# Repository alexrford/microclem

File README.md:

# microclem

`microclem` is a homebrew computer based around the WDC 65C02 processor. Physically, it uses the Eurocard (100x160mm) PCB form factor and type DIN 41612 type C connectors (64 or optionally 96 pin).

Currently only a barebones base board is designed. This board has only very basic functionality (memory, boot ROM, 65C22 for I/O over the external bus). It's designed to be expanded using other cards on a DIN 41612 backplane.

This is in an early stage of development and may not be functional yet.

## Credits

- DIN 41612 footprints are taken from the [official `kicad-footprints` repo](https://github.com/KiCad/kicad-footprints)
- System/bus clock switching component taken from an [EE times article by Rafey Mahmud](https://www.eetimes.com/techniques-to-make-clock-switching-glitch-free/)
- [Ben Eater's 6502 computer](https://eater.net/6502) was the initial inspiration for this project
- Arduino monitor PCB layout based on measurements from [Wayne and Layne](https://www.wayneandlayne.com/blog/2010/12/19/nice-drawings-of-the-arduino-uno-and-mega-2560/)

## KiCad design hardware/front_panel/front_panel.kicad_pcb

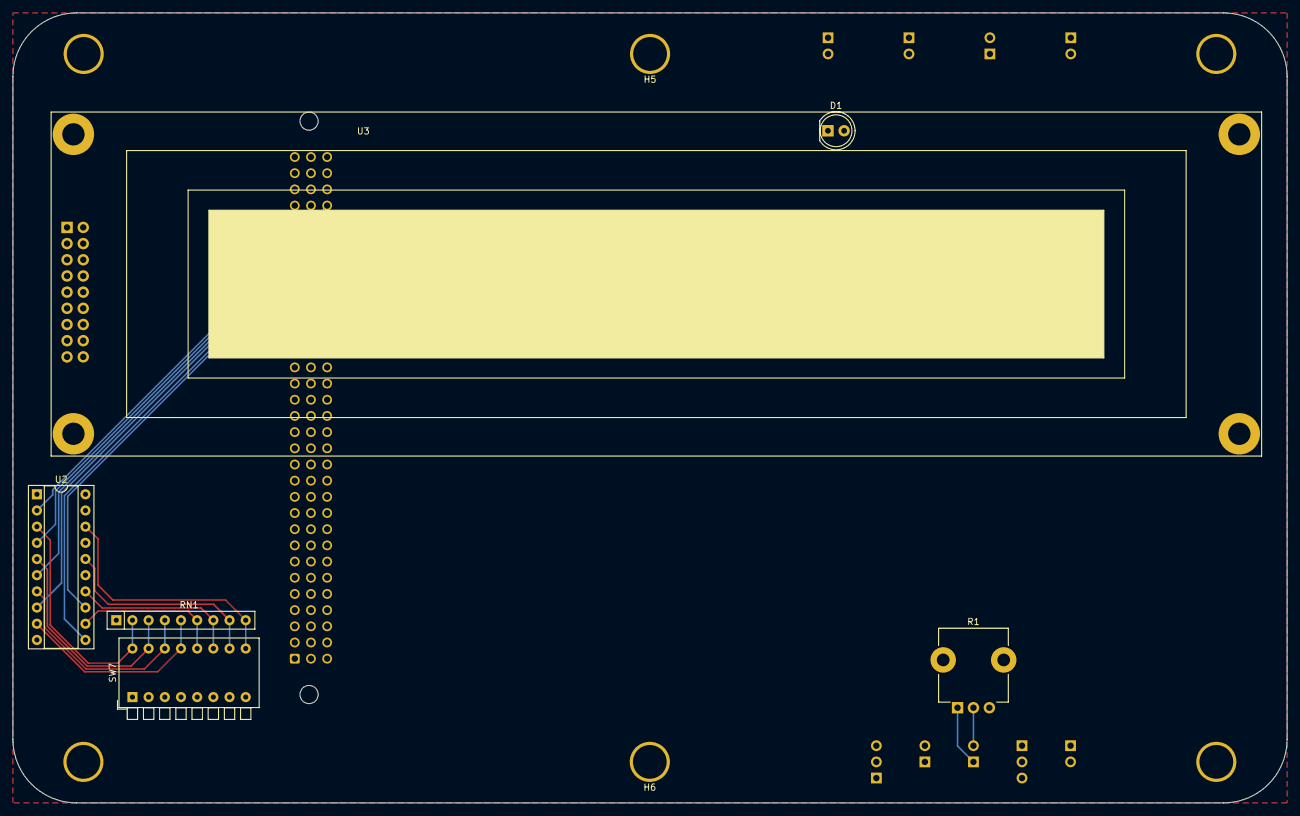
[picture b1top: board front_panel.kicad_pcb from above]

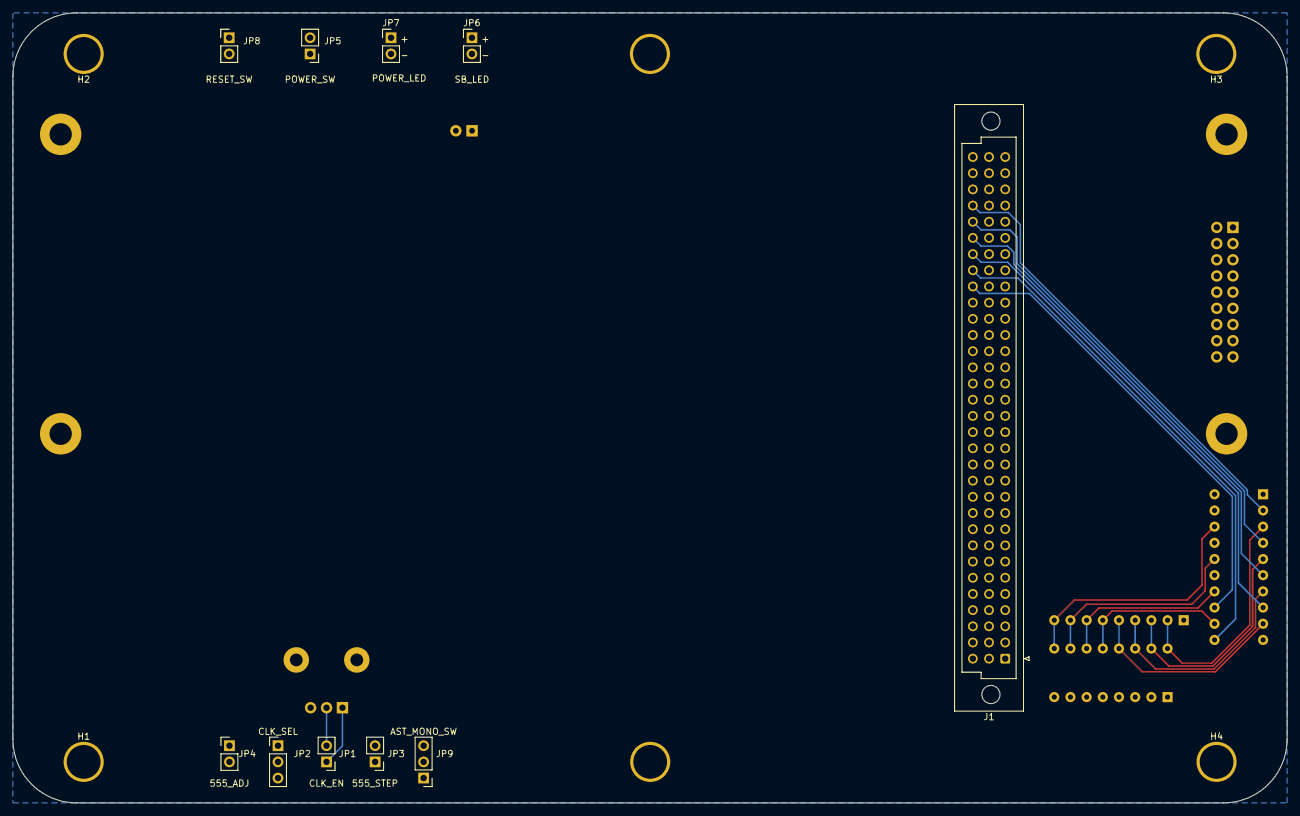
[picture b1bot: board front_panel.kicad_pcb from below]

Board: 2 copper layers, 200.0 x 124.0 mm, 22 parts (14 on the bottom side), 20 nets.

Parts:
D1: LED; LED_D5.0mm
H1, H2, H3, H4, H5, H6: MountingHole; m5-close
J1: C96ABC; DIN41612_C_3x32_Female_Vertical_THT
JP1, JP3, JP4, JP5, JP6, JP7, JP8: Conn_02x01; PinHeader_1x02_P2.54mm_Vertical
JP2, JP9: Conn_01x03_Male; PinHeader_1x03_P2.54mm_Vertical
R1: 100k; Potentiometer_TT_P0915N
RN1: R_Network08; R_Array_SIP9
SW7: SW_DIP_x08; SW_DIP_SPSTx08_Piano_10.8x21.88mm_W7.62mm_P2.54mm
U2: 74HC688; DIP-20_W7.62mm_Socket
U3: NHD-0440WH; NHD-0040WH

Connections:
/bd0: J1.C29, U2.2
/bd1: J1.C28, U2.4
/bd2: J1.C27, U2.6
/bd3: J1.C26, U2.8
/bd4: J1.C25, U2.11
/bd5: J1.C24, U2.13
GND: J1.A32, J1.B32, J1.C32, SW7.1, SW7.2, SW7.3, SW7.4, SW7.5, SW7.6, SW7.7, SW7.8, U2.10, U3.13
unnamed: D1.1, JP6.2
unnamed: D1.2, JP6.1
unnamed: JP1.1, R1.1
unnamed: JP1.2, R1.2
unnamed: RN1.2, SW7.16, U2.3
unnamed: RN1.3, SW7.15, U2.5
unnamed: RN1.4, SW7.14, U2.7
unnamed: RN1.5, SW7.13, U2.9
unnamed: RN1.6, SW7.12, U2.12
unnamed: RN1.7, SW7.11, U2.14
unnamed: RN1.8, SW7.10, U2.16
unnamed: RN1.9, SW7.9, U2.18
VCC: J1.A1, J1.B1, J1.C1, RN1.1, U2.20, U3.14

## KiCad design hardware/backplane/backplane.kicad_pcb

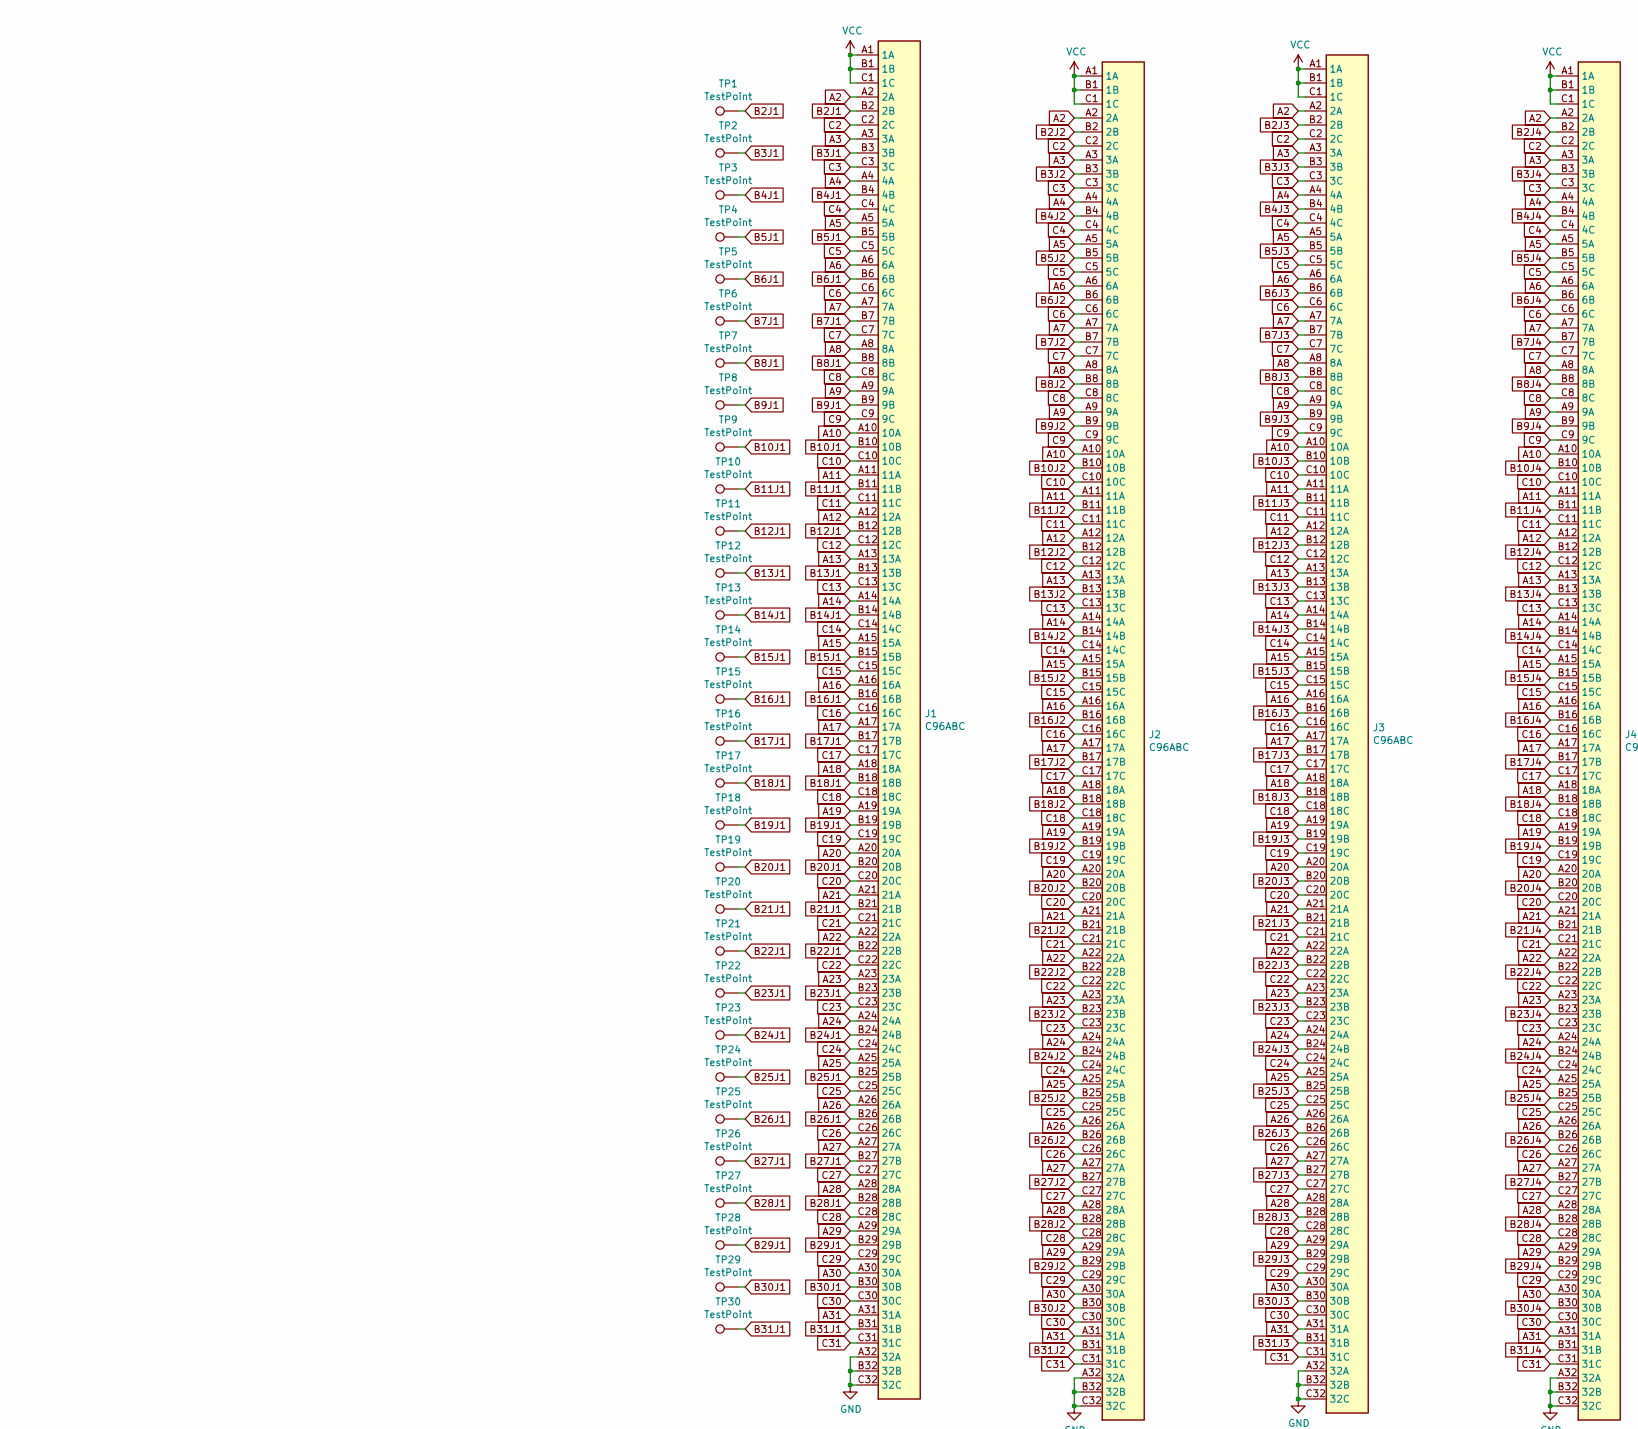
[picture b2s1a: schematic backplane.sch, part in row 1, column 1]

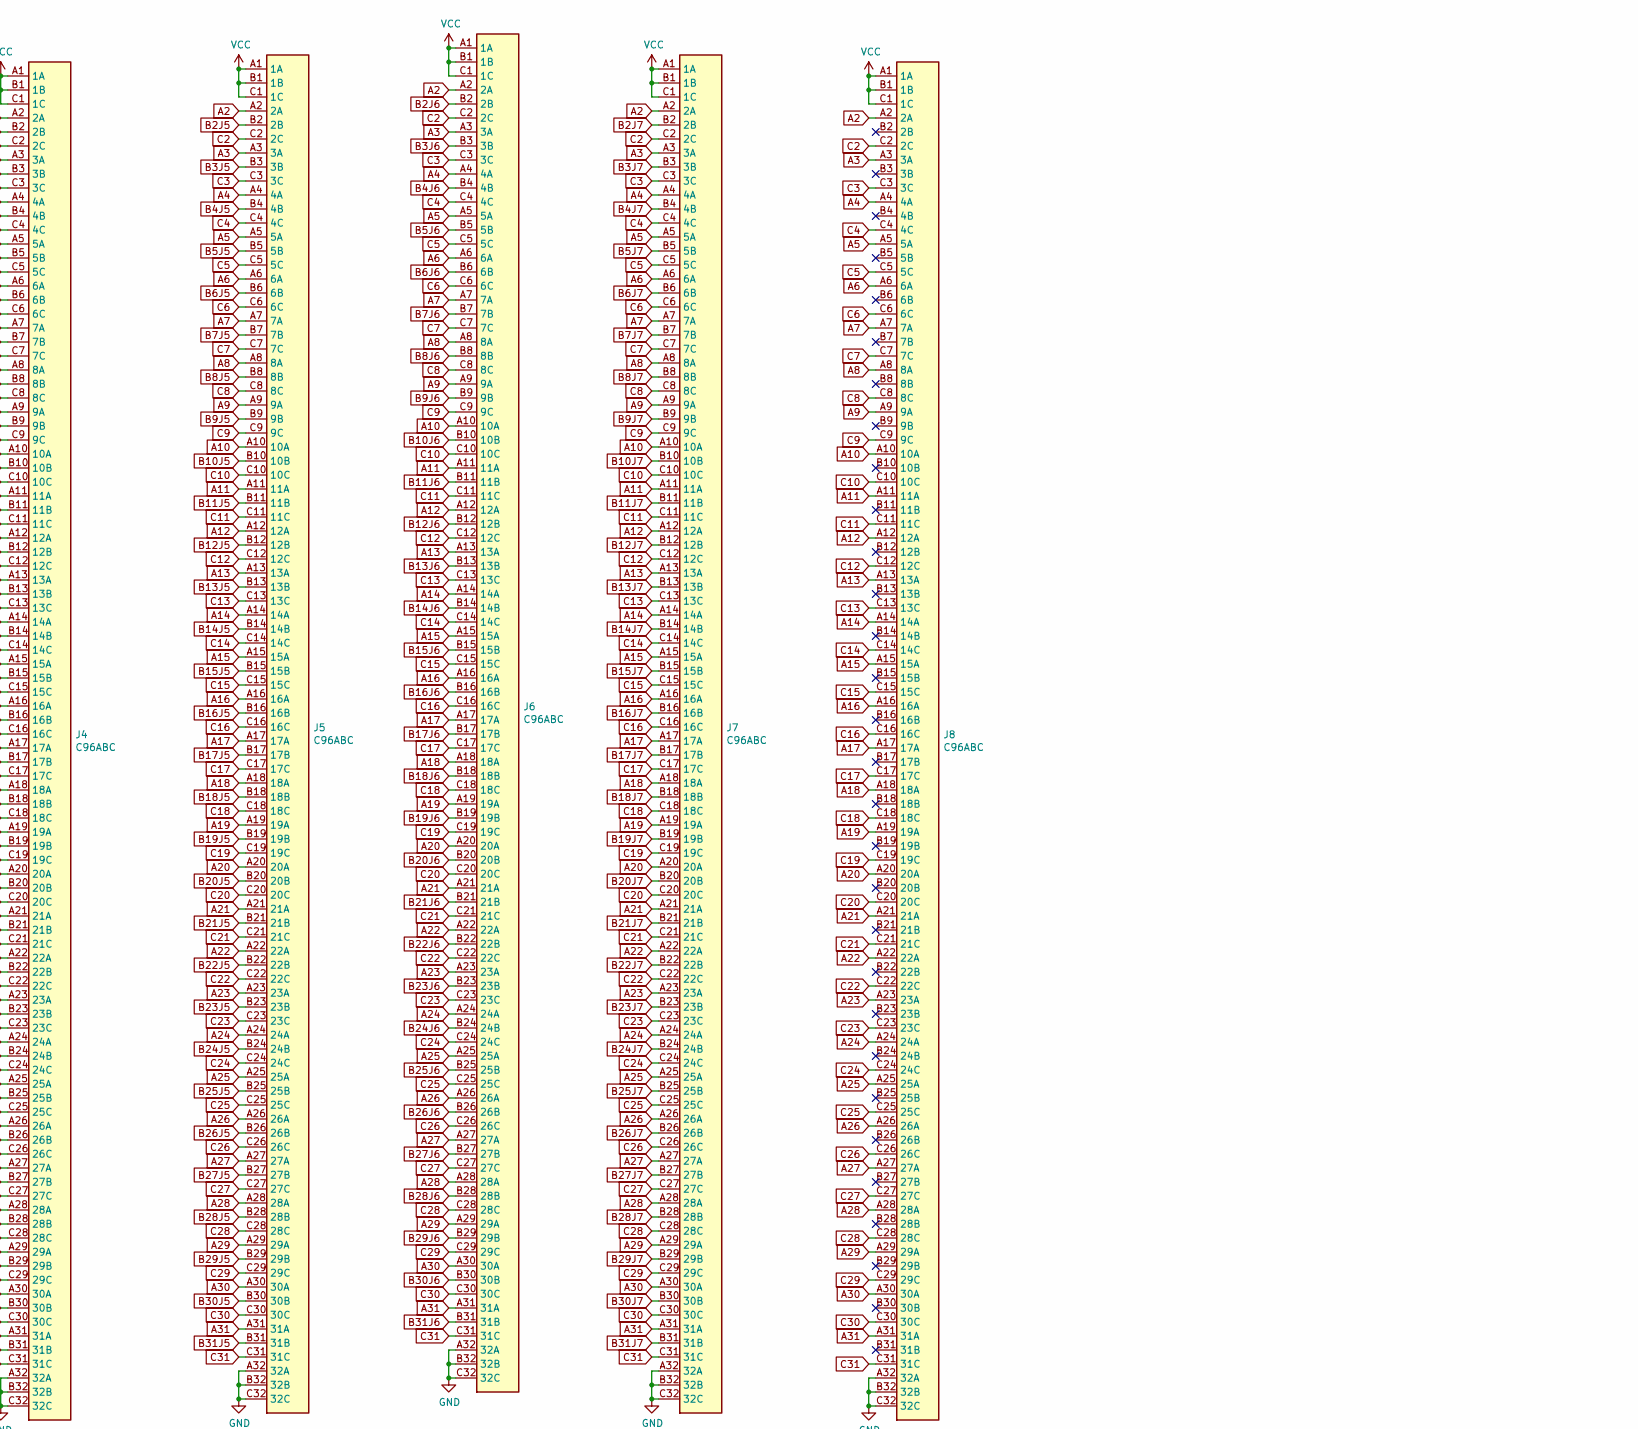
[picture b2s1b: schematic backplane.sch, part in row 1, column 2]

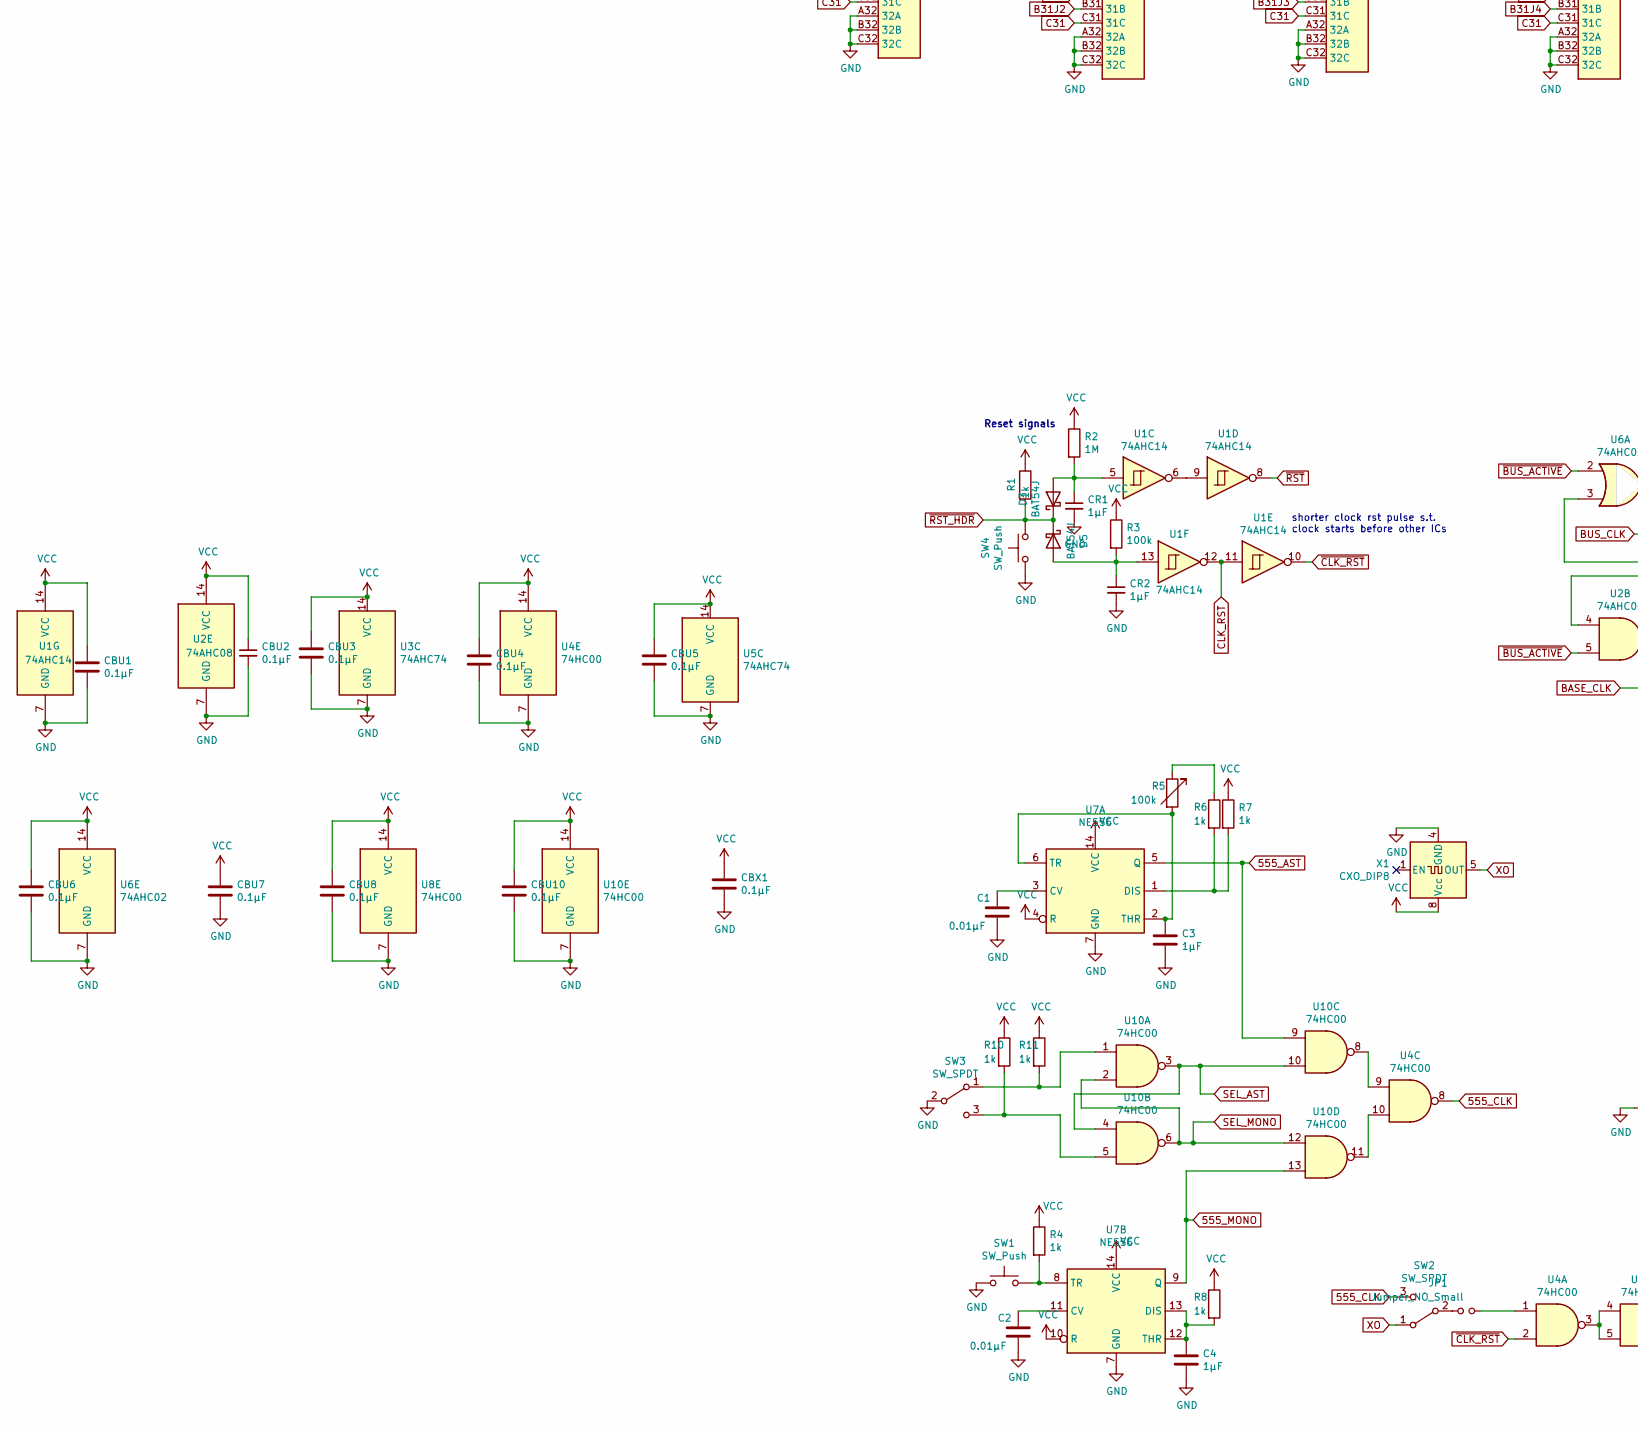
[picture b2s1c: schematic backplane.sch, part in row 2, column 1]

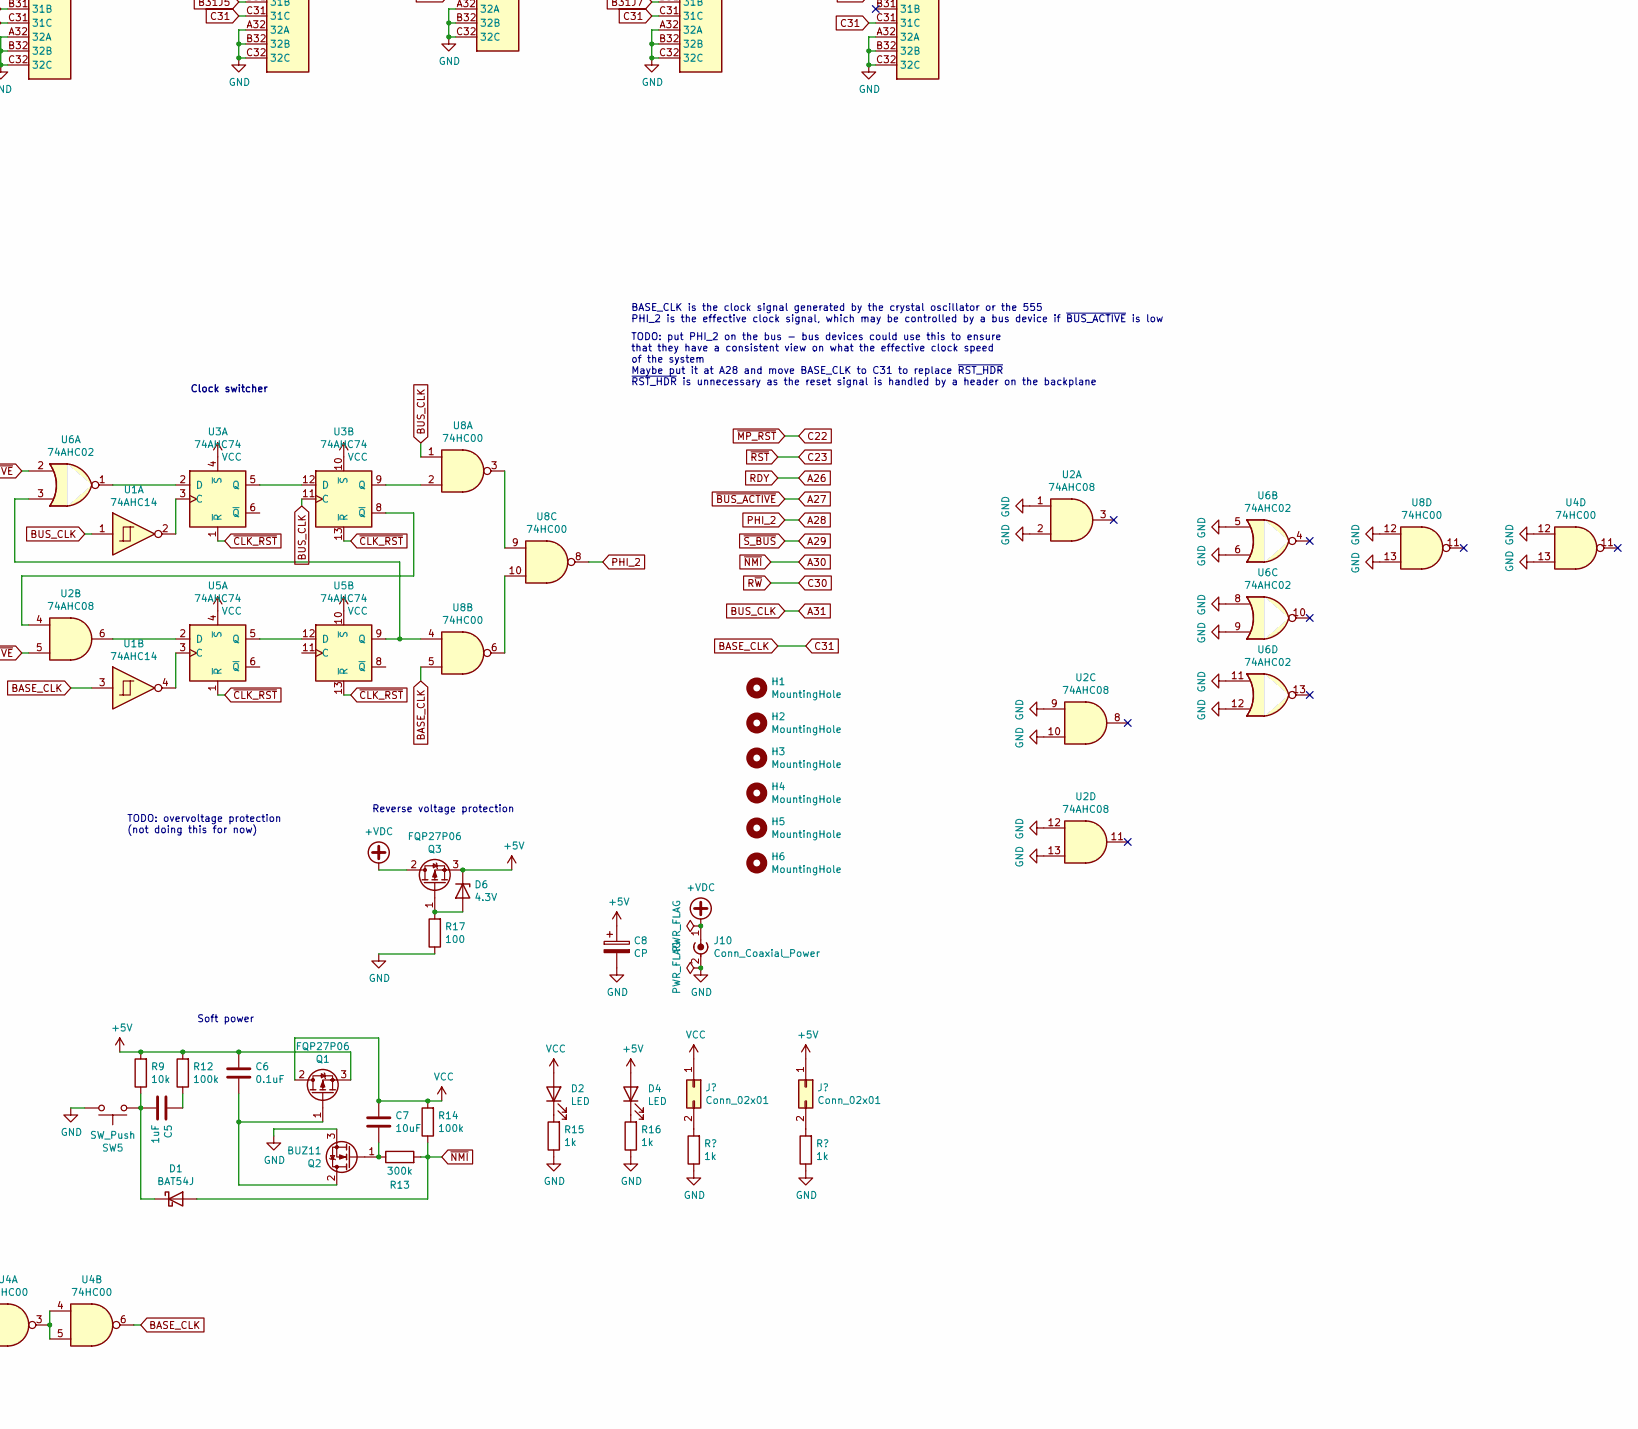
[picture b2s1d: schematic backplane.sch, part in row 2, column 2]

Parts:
C1, C2: 0.01μF; C_0805_2012Metric_Pad1.18x1.45mm_HandSolder
C3, C4: 1μF; C_0805_2012Metric_Pad1.18x1.45mm_HandSolder
C5: 1uF; C_Axial_L5.1mm_D3.1mm_P7.50mm_Horizontal
C6: 0.1uF; C_Disc_D4.7mm_W2.5mm_P5.00mm
C7: 10uF; C_Axial_L5.1mm_D3.1mm_P7.50mm_Horizontal
C8: CP; CP_Radial_D10.0mm_P5.00mm
CBU1, CBU2, CBU3, CBU4, CBU5, CBU6, CBU7, CBU8, CBU10: 0.1μF; C_0805_2012Metric_Pad1.18x1.45mm_HandSolder
CBX1: 0.1μF; C_0805_2012Metric_Pad1.18x1.45mm_HandSolder
CR1, CR2: 1μF; C_0805_2012Metric_Pad1.18x1.45mm_HandSolder
D1, D3, D5: BAT54J; D_A-405_P7.62mm_Horizontal
D2, D4: LED; LED_D3.0mm
D6: 4.3V; D_A-405_P7.62mm_Horizontal
H1, H2, H3, H4, H5, H6: MountingHole; m5-close
J1, J2, J3, J4, J5, J6, J7, J8: C96ABC; DIN41612_C_3x32_Female_Vertical_THT
J10: Conn_Coaxial_Power; AMASS_XT60-M_1x02_P7.20mm_Vertical
JP1: Jumper_NO_Small; PinHeader_1x02_P2.54mm_Vertical
Q1, Q3: FQP27P06; TO-220-3_Vertical
Q2: BUZ11; TO-220-3_Vertical
R1, R4, R6, R7, R8, R10, R11: 1k; R_0805_2012Metric_Pad1.20x1.40mm_HandSolder
R2: 1M; R_0805_2012Metric_Pad1.20x1.40mm_HandSolder
R3: 100k; R_0805_2012Metric_Pad1.20x1.40mm_HandSolder
R5: 100k; PinHeader_1x02_P2.54mm_Vertical
R9: 10k; R_Axial_DIN0207_L6.3mm_D2.5mm_P7.62mm_Horizontal
R12, R14: 100k; R_Axial_DIN0207_L6.3mm_D2.5mm_P7.62mm_Horizontal
R13: 300k; R_Axial_DIN0207_L6.3mm_D2.5mm_P7.62mm_Horizontal
R15, R16: 1k; R_Axial_DIN0207_L6.3mm_D2.5mm_P7.62mm_Horizontal
R17: 100; R_Axial_DIN0207_L6.3mm_D2.5mm_P7.62mm_Horizontal
SW1, SW4, SW5: SW_Push; PinHeader_1x02_P2.54mm_Vertical
SW2, SW3: SW_SPDT; PinHeader_1x03_P2.54mm_Vertical
TP1, TP2, TP3, TP4, TP5, TP6, TP7, TP8, TP9, TP10, TP11, TP12, TP13, TP14, TP15, TP16, TP17, TP18, TP19, TP20, TP21, TP22, TP23, TP24, TP25, TP26, TP27, TP28, TP29, TP30: TestPoint; TestPoint_THTPad_D1.0mm_Drill0.5mm
U1: 74AHC14; SOIC-14_3.9x8.7mm_P1.27mm
U2: 74AHC08; SOIC-14_3.9x8.7mm_P1.27mm
U3, U5: 74AHC74; SOIC-14_3.9x8.7mm_P1.27mm
U4, U8, U10: 74HC00; SOIC-14_3.9x8.7mm_P1.27mm
U6: 74AHC02; SOIC-14_3.9x8.7mm_P1.27mm
U7: NE556; SOIC-14_3.9x8.7mm_P1.27mm
X1: CXO_DIP8; DIP-8_W7.62mm_Socket

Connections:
555_AST: U7.5 (Q), U10.9
555_CLK: SW2.3 (C), U4.8
555_MONO: U7.9 (Q), U10.13
+5V: C6.1, C8.1, D4.2 (A), D6.1 (K), Q1.3 (S), Q3.3 (S), R9.2, R12.2; also elsewhere on the board
+VDC: J10.1 (In), Q3.2 (D)
A2: J1.A2 (2A), J2.A2 (2A), J3.A2 (2A), J4.A2 (2A), J5.A2 (2A), J6.A2 (2A), J7.A2 (2A), J8.A2 (2A)
A3: J1.A3 (3A), J2.A3 (3A), J3.A3 (3A), J4.A3 (3A), J5.A3 (3A), J6.A3 (3A), J7.A3 (3A), J8.A3 (3A)
A4: J1.A4 (4A), J2.A4 (4A), J3.A4 (4A), J4.A4 (4A), J5.A4 (4A), J6.A4 (4A), J7.A4 (4A), J8.A4 (4A)
A5: J1.A5 (5A), J2.A5 (5A), J3.A5 (5A), J4.A5 (5A), J5.A5 (5A), J6.A5 (5A), J7.A5 (5A), J8.A5 (5A)
A6: J1.A6 (6A), J2.A6 (6A), J3.A6 (6A), J4.A6 (6A), J5.A6 (6A), J6.A6 (6A), J7.A6 (6A), J8.A6 (6A)
A7: J1.A7 (7A), J2.A7 (7A), J3.A7 (7A), J4.A7 (7A), J5.A7 (7A), J6.A7 (7A), J7.A7 (7A), J8.A7 (7A)
A8: J1.A8 (8A), J2.A8 (8A), J3.A8 (8A), J4.A8 (8A), J5.A8 (8A), J6.A8 (8A), J7.A8 (8A), J8.A8 (8A)
A9: J1.A9 (9A), J2.A9 (9A), J3.A9 (9A), J4.A9 (9A), J5.A9 (9A), J6.A9 (9A), J7.A9 (9A), J8.A9 (9A)
A10: J1.A10 (10A), J2.A10 (10A), J3.A10 (10A), J4.A10 (10A), J5.A10 (10A), J6.A10 (10A), J7.A10 (10A), J8.A10 (10A)
A11: J1.A11 (11A), J2.A11 (11A), J3.A11 (11A), J4.A11 (11A), J5.A11 (11A), J6.A11 (11A), J7.A11 (11A), J8.A11 (11A)
A12: J1.A12 (12A), J2.A12 (12A), J3.A12 (12A), J4.A12 (12A), J5.A12 (12A), J6.A12 (12A), J7.A12 (12A), J8.A12 (12A)
A13: J1.A13 (13A), J2.A13 (13A), J3.A13 (13A), J4.A13 (13A), J5.A13 (13A), J6.A13 (13A), J7.A13 (13A), J8.A13 (13A)
A14: J1.A14 (14A), J2.A14 (14A), J3.A14 (14A), J4.A14 (14A), J5.A14 (14A), J6.A14 (14A), J7.A14 (14A), J8.A14 (14A)
A15: J1.A15 (15A), J2.A15 (15A), J3.A15 (15A), J4.A15 (15A), J5.A15 (15A), J6.A15 (15A), J7.A15 (15A), J8.A15 (15A)
A16: J1.A16 (16A), J2.A16 (16A), J3.A16 (16A), J4.A16 (16A), J5.A16 (16A), J6.A16 (16A), J7.A16 (16A), J8.A16 (16A)
A17: J1.A17 (17A), J2.A17 (17A), J3.A17 (17A), J4.A17 (17A), J5.A17 (17A), J6.A17 (17A), J7.A17 (17A), J8.A17 (17A)
A18: J1.A18 (18A), J2.A18 (18A), J3.A18 (18A), J4.A18 (18A), J5.A18 (18A), J6.A18 (18A), J7.A18 (18A), J8.A18 (18A)
A19: J1.A19 (19A), J2.A19 (19A), J3.A19 (19A), J4.A19 (19A), J5.A19 (19A), J6.A19 (19A), J7.A19 (19A), J8.A19 (19A)
A20: J1.A20 (20A), J2.A20 (20A), J3.A20 (20A), J4.A20 (20A), J5.A20 (20A), J6.A20 (20A), J7.A20 (20A), J8.A20 (20A)
A21: J1.A21 (21A), J2.A21 (21A), J3.A21 (21A), J4.A21 (21A), J5.A21 (21A), J6.A21 (21A), J7.A21 (21A), J8.A21 (21A)
A22: J1.A22 (22A), J2.A22 (22A), J3.A22 (22A), J4.A22 (22A), J5.A22 (22A), J6.A22 (22A), J7.A22 (22A), J8.A22 (22A)
A23: J1.A23 (23A), J2.A23 (23A), J3.A23 (23A), J4.A23 (23A), J5.A23 (23A), J6.A23 (23A), J7.A23 (23A), J8.A23 (23A)
A24: J1.A24 (24A), J2.A24 (24A), J3.A24 (24A), J4.A24 (24A), J5.A24 (24A), J6.A24 (24A), J7.A24 (24A), J8.A24 (24A)
A25: J1.A25 (25A), J2.A25 (25A), J3.A25 (25A), J4.A25 (25A), J5.A25 (25A), J6.A25 (25A), J7.A25 (25A), J8.A25 (25A)
A26: J1.A26 (26A), J2.A26 (26A), J3.A26 (26A), J4.A26 (26A), J5.A26 (26A), J6.A26 (26A), J7.A26 (26A), J8.A26 (26A)
A27: J1.A27 (27A), J2.A27 (27A), J3.A27 (27A), J4.A27 (27A), J5.A27 (27A), J6.A27 (27A), J7.A27 (27A), J8.A27 (27A), U2.5, U6.2
A28: J1.A28 (28A), J2.A28 (28A), J3.A28 (28A), J4.A28 (28A), J5.A28 (28A), J6.A28 (28A), J7.A28 (28A), J8.A28 (28A), U8.8
A29: J1.A29 (29A), J2.A29 (29A), J3.A29 (29A), J4.A29 (29A), J5.A29 (29A), J6.A29 (29A), J7.A29 (29A), J8.A29 (29A)
A30: D1.2 (A), J1.A30 (30A), J2.A30 (30A), J3.A30 (30A), J4.A30 (30A), J5.A30 (30A), J6.A30 (30A), J7.A30 (30A), J8.A30 (30A), R13.2, R14.1
A31: J1.A31 (31A), J2.A31 (31A), J3.A31 (31A), J4.A31 (31A), J5.A31 (31A), J6.A31 (31A), J7.A31 (31A), J8.A31 (31A), U1.1, U3.11 (C), U8.1
B2J1: J1.B2 (2B), TP1.1
B2J2: J2.B2 (2B)
B2J3: J3.B2 (2B)
B2J4: J4.B2 (2B)
B2J5: J5.B2 (2B)
B2J6: J6.B2 (2B)
B2J7: J7.B2 (2B)
B3J1: J1.B3 (3B), TP2.1
B3J2: J2.B3 (3B)
B3J3: J3.B3 (3B)
B3J4: J4.B3 (3B)
B3J5: J5.B3 (3B)
B3J6: J6.B3 (3B)
B3J7: J7.B3 (3B)
B4J1: J1.B4 (4B), TP3.1
B4J2: J2.B4 (4B)
B4J3: J3.B4 (4B)
B4J4: J4.B4 (4B)
B4J5: J5.B4 (4B)
B4J6: J6.B4 (4B)
B4J7: J7.B4 (4B)
B5J1: J1.B5 (5B), TP4.1
B5J2: J2.B5 (5B)
B5J3: J3.B5 (5B)
B5J4: J4.B5 (5B)
B5J5: J5.B5 (5B)
B5J6: J6.B5 (5B)
B5J7: J7.B5 (5B)
B6J1: J1.B6 (6B), TP5.1
B6J2: J2.B6 (6B)
B6J3: J3.B6 (6B)
B6J4: J4.B6 (6B)
B6J5: J5.B6 (6B)
B6J6: J6.B6 (6B)
B6J7: J7.B6 (6B)
B7J1: J1.B7 (7B), TP6.1
B7J2: J2.B7 (7B)
B7J3: J3.B7 (7B)
B7J4: J4.B7 (7B)
B7J5: J5.B7 (7B)
B7J6: J6.B7 (7B)
B7J7: J7.B7 (7B)
B8J1: J1.B8 (8B), TP7.1
B8J2: J2.B8 (8B)
B8J3: J3.B8 (8B)
B8J4: J4.B8 (8B)
B8J5: J5.B8 (8B)
B8J6: J6.B8 (8B)
B8J7: J7.B8 (8B)
B9J1: J1.B9 (9B), TP8.1
B9J2: J2.B9 (9B)
B9J3: J3.B9 (9B)
B9J4: J4.B9 (9B)
B9J5: J5.B9 (9B)
B9J6: J6.B9 (9B)
B9J7: J7.B9 (9B)
B10J1: J1.B10 (10B), TP9.1
B10J2: J2.B10 (10B)
B10J3: J3.B10 (10B)
B10J4: J4.B10 (10B)
B10J5: J5.B10 (10B)
B10J6: J6.B10 (10B)
B10J7: J7.B10 (10B)
B11J1: J1.B11 (11B), TP10.1
B11J2: J2.B11 (11B)
B11J3: J3.B11 (11B)
B11J4: J4.B11 (11B)
B11J5: J5.B11 (11B)
B11J6: J6.B11 (11B)
B11J7: J7.B11 (11B)
B12J1: J1.B12 (12B), TP11.1
B12J2: J2.B12 (12B)
B12J3: J3.B12 (12B)
B12J4: J4.B12 (12B)
B12J5: J5.B12 (12B)
B12J6: J6.B12 (12B)
B12J7: J7.B12 (12B)
B13J1: J1.B13 (13B), TP12.1
B13J2: J2.B13 (13B)
B13J3: J3.B13 (13B)
B13J4: J4.B13 (13B)
B13J5: J5.B13 (13B)
B13J6: J6.B13 (13B)
B13J7: J7.B13 (13B)
B14J1: J1.B14 (14B), TP13.1
B14J2: J2.B14 (14B)
B14J3: J3.B14 (14B)
B14J4: J4.B14 (14B)
B14J5: J5.B14 (14B)
B14J6: J6.B14 (14B)
B14J7: J7.B14 (14B)
B15J1: J1.B15 (15B), TP14.1
B15J2: J2.B15 (15B)
B15J3: J3.B15 (15B)
B15J4: J4.B15 (15B)
B15J5: J5.B15 (15B)
B15J6: J6.B15 (15B)
B15J7: J7.B15 (15B)
B16J1: J1.B16 (16B), TP15.1
B16J2: J2.B16 (16B)
B16J3: J3.B16 (16B)
B16J4: J4.B16 (16B)
B16J5: J5.B16 (16B)
B16J6: J6.B16 (16B)
B16J7: J7.B16 (16B)
B17J1: J1.B17 (17B), TP16.1
B17J2: J2.B17 (17B)
B17J3: J3.B17 (17B)
B17J4: J4.B17 (17B)
B17J5: J5.B17 (17B)
B17J6: J6.B17 (17B)
B17J7: J7.B17 (17B)
B18J1: J1.B18 (18B), TP17.1
B18J2: J2.B18 (18B)
B18J3: J3.B18 (18B)
B18J4: J4.B18 (18B)
B18J5: J5.B18 (18B)
B18J6: J6.B18 (18B)
B18J7: J7.B18 (18B)
B19J1: J1.B19 (19B), TP18.1
B19J2: J2.B19 (19B)
B19J3: J3.B19 (19B)
B19J4: J4.B19 (19B)
B19J5: J5.B19 (19B)
B19J6: J6.B19 (19B)
B19J7: J7.B19 (19B)
B20J1: J1.B20 (20B), TP19.1
B20J2: J2.B20 (20B)
B20J3: J3.B20 (20B)
B20J4: J4.B20 (20B)
B20J5: J5.B20 (20B)
B20J6: J6.B20 (20B)
B20J7: J7.B20 (20B)
B21J1: J1.B21 (21B), TP20.1
B21J2: J2.B21 (21B)
B21J3: J3.B21 (21B)
B21J4: J4.B21 (21B)
B21J5: J5.B21 (21B)
B21J6: J6.B21 (21B)
B21J7: J7.B21 (21B)
B22J1: J1.B22 (22B), TP21.1
B22J2: J2.B22 (22B)
B22J3: J3.B22 (22B)
B22J4: J4.B22 (22B)
B22J5: J5.B22 (22B)
B22J6: J6.B22 (22B)
B22J7: J7.B22 (22B)
B23J1: J1.B23 (23B), TP22.1
B23J2: J2.B23 (23B)
B23J3: J3.B23 (23B)
B23J4: J4.B23 (23B)
B23J5: J5.B23 (23B)
B23J6: J6.B23 (23B)
B23J7: J7.B23 (23B)
B24J1: J1.B24 (24B), TP23.1
B24J2: J2.B24 (24B)
B24J3: J3.B24 (24B)
B24J4: J4.B24 (24B)
B24J5: J5.B24 (24B)
B24J6: J6.B24 (24B)
B24J7: J7.B24 (24B)
B25J1: J1.B25 (25B), TP24.1
B25J2: J2.B25 (25B)
B25J3: J3.B25 (25B)
B25J4: J4.B25 (25B)
B25J5: J5.B25 (25B)
B25J6: J6.B25 (25B)
B25J7: J7.B25 (25B)
B26J1: J1.B26 (26B), TP25.1
B26J2: J2.B26 (26B)
B26J3: J3.B26 (26B)
B26J4: J4.B26 (26B)
B26J5: J5.B26 (26B)
B26J6: J6.B26 (26B)
B26J7: J7.B26 (26B)
B27J1: J1.B27 (27B), TP26.1
B27J2: J2.B27 (27B)
B27J3: J3.B27 (27B)
B27J4: J4.B27 (27B)
B27J5: J5.B27 (27B)
B27J6: J6.B27 (27B)
B27J7: J7.B27 (27B)
B28J1: J1.B28 (28B), TP27.1
B28J2: J2.B28 (28B)
B28J3: J3.B28 (28B)
B28J4: J4.B28 (28B)
B28J5: J5.B28 (28B)
B28J6: J6.B28 (28B)
B28J7: J7.B28 (28B)
B29J1: J1.B29 (29B), TP28.1
B29J2: J2.B29 (29B)
B29J3: J3.B29 (29B)
B29J4: J4.B29 (29B)
B29J5: J5.B29 (29B)
B29J6: J6.B29 (29B)
B29J7: J7.B29 (29B)
B30J1: J1.B30 (30B), TP29.1
B30J2: J2.B30 (30B)
B30J3: J3.B30 (30B)
B30J4: J4.B30 (30B)
B30J5: J5.B30 (30B)
B30J6: J6.B30 (30B)
B30J7: J7.B30 (30B)
B31J1: J1.B31 (31B), TP30.1
B31J2: J2.B31 (31B)
B31J3: J3.B31 (31B)
B31J4: J4.B31 (31B)
B31J5: J5.B31 (31B)
B31J6: J6.B31 (31B)
B31J7: J7.B31 (31B)
BASE_CLK: J1.C31 (31C), J2.C31 (31C), J3.C31 (31C), J4.C31 (31C), J5.C31 (31C), J6.C31 (31C), J7.C31 (31C), J8.C31 (31C), U1.3, U4.6, U8.5
C2: J1.C2 (2C), J2.C2 (2C), J3.C2 (2C), J4.C2 (2C), J5.C2 (2C), J6.C2 (2C), J7.C2 (2C), J8.C2 (2C)
C3: J1.C3 (3C), J2.C3 (3C), J3.C3 (3C), J4.C3 (3C), J5.C3 (3C), J6.C3 (3C), J7.C3 (3C), J8.C3 (3C)
C4: J1.C4 (4C), J2.C4 (4C), J3.C4 (4C), J4.C4 (4C), J5.C4 (4C), J6.C4 (4C), J7.C4 (4C), J8.C4 (4C)
C5: J1.C5 (5C), J2.C5 (5C), J3.C5 (5C), J4.C5 (5C), J5.C5 (5C), J6.C5 (5C), J7.C5 (5C), J8.C5 (5C)
C6: J1.C6 (6C), J2.C6 (6C), J3.C6 (6C), J4.C6 (6C), J5.C6 (6C), J6.C6 (6C), J7.C6 (6C), J8.C6 (6C)
C7: J1.C7 (7C), J2.C7 (7C), J3.C7 (7C), J4.C7 (7C), J5.C7 (7C), J6.C7 (7C), J7.C7 (7C), J8.C7 (7C)
C8: J1.C8 (8C), J2.C8 (8C), J3.C8 (8C), J4.C8 (8C), J5.C8 (8C), J6.C8 (8C), J7.C8 (8C), J8.C8 (8C)
C9: J1.C9 (9C), J2.C9 (9C), J3.C9 (9C), J4.C9 (9C), J5.C9 (9C), J6.C9 (9C), J7.C9 (9C), J8.C9 (9C)
C10: J1.C10 (10C), J2.C10 (10C), J3.C10 (10C), J4.C10 (10C), J5.C10 (10C), J6.C10 (10C), J7.C10 (10C), J8.C10 (10C)
C11: J1.C11 (11C), J2.C11 (11C), J3.C11 (11C), J4.C11 (11C), J5.C11 (11C), J6.C11 (11C), J7.C11 (11C), J8.C11 (11C)
C12: J1.C12 (12C), J2.C12 (12C), J3.C12 (12C), J4.C12 (12C), J5.C12 (12C), J6.C12 (12C), J7.C12 (12C), J8.C12 (12C)
C13: J1.C13 (13C), J2.C13 (13C), J3.C13 (13C), J4.C13 (13C), J5.C13 (13C), J6.C13 (13C), J7.C13 (13C), J8.C13 (13C)
C14: J1.C14 (14C), J2.C14 (14C), J3.C14 (14C), J4.C14 (14C), J5.C14 (14C), J6.C14 (14C), J7.C14 (14C), J8.C14 (14C)
C15: J1.C15 (15C), J2.C15 (15C), J3.C15 (15C), J4.C15 (15C), J5.C15 (15C), J6.C15 (15C), J7.C15 (15C), J8.C15 (15C)
C16: J1.C16 (16C), J2.C16 (16C), J3.C16 (16C), J4.C16 (16C), J5.C16 (16C), J6.C16 (16C), J7.C16 (16C), J8.C16 (16C)
C17: J1.C17 (17C), J2.C17 (17C), J3.C17 (17C), J4.C17 (17C), J5.C17 (17C), J6.C17 (17C), J7.C17 (17C), J8.C17 (17C)
C18: J1.C18 (18C), J2.C18 (18C), J3.C18 (18C), J4.C18 (18C), J5.C18 (18C), J6.C18 (18C), J7.C18 (18C), J8.C18 (18C)
C19: J1.C19 (19C), J2.C19 (19C), J3.C19 (19C), J4.C19 (19C), J5.C19 (19C), J6.C19 (19C), J7.C19 (19C), J8.C19 (19C)
C20: J1.C20 (20C), J2.C20 (20C), J3.C20 (20C), J4.C20 (20C), J5.C20 (20C), J6.C20 (20C), J7.C20 (20C), J8.C20 (20C)
C21: J1.C21 (21C), J2.C21 (21C), J3.C21 (21C), J4.C21 (21C), J5.C21 (21C), J6.C21 (21C), J7.C21 (21C), J8.C21 (21C)
C22: J1.C22 (22C), J2.C22 (22C), J3.C22 (22C), J4.C22 (22C), J5.C22 (22C), J6.C22 (22C), J7.C22 (22C), J8.C22 (22C)
C23: J1.C23 (23C), J2.C23 (23C), J3.C23 (23C), J4.C23 (23C), J5.C23 (23C), J6.C23 (23C), J7.C23 (23C), J8.C23 (23C), U1.8
C24: J1.C24 (24C), J2.C24 (24C), J3.C24 (24C), J4.C24 (24C), J5.C24 (24C), J6.C24 (24C), J7.C24 (24C), J8.C24 (24C)
C25: J1.C25 (25C), J2.C25 (25C), J3.C25 (25C), J4.C25 (25C), J5.C25 (25C), J6.C25 (25C), J7.C25 (25C), J8.C25 (25C)
C26: J1.C26 (26C), J2.C26 (26C), J3.C26 (26C), J4.C26 (26C), J5.C26 (26C), J6.C26 (26C), J7.C26 (26C), J8.C26 (26C)
C27: J1.C27 (27C), J2.C27 (27C), J3.C27 (27C), J4.C27 (27C), J5.C27 (27C), J6.C27 (27C), J7.C27 (27C), J8.C27 (27C)
C28: J1.C28 (28C), J2.C28 (28C), J3.C28 (28C), J4.C28 (28C), J5.C28 (28C), J6.C28 (28C), J7.C28 (28C), J8.C28 (28C)
C29: J1.C29 (29C), J2.C29 (29C), J3.C29 (29C), J4.C29 (29C), J5.C29 (29C), J6.C29 (29C), J7.C29 (29C), J8.C29 (29C)
C30: J1.C30 (30C), J2.C30 (30C), J3.C30 (30C), J4.C30 (30C), J5.C30 (30C), J6.C30 (30C), J7.C30 (30C), J8.C30 (30C)
CLK_RST: U1.11, U1.12
GND: C1.2, C2.2, C3.2, C4.2, C8.2, CBU1.2, CBU2.2, CBU3.2, CBU4.2, CBU5.2, CBU6.2, CBU7.2, CBU8.2, CBU10.2, CBX1.2, CR1.2, CR2.2, J1.A32 (32A), J1.B32 (32B), J1.C32 (32C), J2.A32 (32A), J2.B32 (32B), J2.C32 (32C), J3.A32 (32A), J3.B32 (32B), J3.C32 (32C), J4.A32 (32A), J4.B32 (32B), J4.C32 (32C), J5.A32 (32A), J5.B32 (32B), J5.C32 (32C), J6.A32 (32A), J6.B32 (32B), J6.C32 (32C), J7.A32 (32A), J7.B32 (32B), J7.C32 (32C), J8.A32 (32A), J8.B32 (32B), J8.C32 (32C), J10.2 (Ext), Q2.3 (S), R15.1, R16.1, R17.1, SW1.1, SW3.2 (B), SW4.1, SW5.2, U1.7 (GND), U2.1, U2.2, U2.7 (GND), U2.9, U2.10, U2.12, U2.13, U3.7 (GND), U4.7 (GND), U4.12, U4.13, U5.7 (GND), U6.5, U6.6, U6.7 (GND), U6.8, U6.9, U6.11, U6.12, U7.7 (GND), U8.7 (GND), U8.12, U8.13, U10.7 (GND), X1.4 (GND); also elsewhere on the board
unnamed: C1.1, U7.3 (CV)
unnamed: C2.1, U7.11 (CV)
unnamed: C3.1, R5.2, U7.2 (THR), U7.6 (TR)
unnamed: C4.1, R8.2, U7.12 (THR), U7.13 (DIS)
unnamed: C5.1, R12.1
unnamed: C5.2, D1.1 (K), R9.1, SW5.1
unnamed: C6.2, Q1.1 (G), Q2.2 (D)
unnamed: C7.2, Q2.1 (G), R13.1
unnamed: CR1.1, D3.2 (A), R2.2, U1.5
unnamed: CR2.1, D5.2 (A), R3.2, U1.13
unnamed: D2.1 (K), R15.2
unnamed: D4.1 (K), R16.2
unnamed: D6.2 (A), Q3.1 (G), R17.2
unnamed: JP1.1, SW2.2 (B)
unnamed: JP1.2, U4.1
unnamed: R4.2, SW1.2, U7.8 (TR)
unnamed: R5.1, R6.1
unnamed: R6.2, R7.2, U7.1 (DIS)
unnamed: R10.2, SW3.3 (C), U10.5
unnamed: R11.2, SW3.1 (A), U10.1
unnamed: U1.2, U3.3 (C)
unnamed: U1.4, U5.3 (C)
unnamed: U1.6, U1.9
unnamed: U2.4, U3.8 (~Q)
unnamed: U2.6, U5.2 (D)
unnamed: U3.2 (D), U6.1
unnamed: U3.9 (Q), U8.2
unnamed: U3.5 (Q), U3.12 (D)
unnamed: U4.3, U4.4, U4.5
unnamed: U5.9 (Q), U6.3, U8.4
unnamed: U5.5 (Q), U5.12 (D)
unnamed: U8.3, U8.9
unnamed: U8.6, U8.10
unnamed: U4.9, U10.8
unnamed: U4.10, U10.11
SEL_AST: U10.3, U10.4, U10.10
SEL_MONO: U10.2, U10.6, U10.12
VCC: C7.1, CBU1.1, CBU2.1, CBU3.1, CBU4.1, CBU5.1, CBU6.1, CBU7.1, CBU8.1, CBU10.1, CBX1.1, D2.2 (A), J1.A1 (1A), J1.B1 (1B), J1.C1 (1C), J2.A1 (1A), J2.B1 (1B), J2.C1 (1C), J3.A1 (1A), J3.B1 (1B), J3.C1 (1C), J4.A1 (1A), J4.B1 (1B), J4.C1 (1C), J5.A1 (1A), J5.B1 (1B), J5.C1 (1C), J6.A1 (1A), J6.B1 (1B), J6.C1 (1C), J7.A1 (1A), J7.B1 (1B), J7.C1 (1C), J8.A1 (1A), J8.B1 (1B), J8.C1 (1C), Q1.2 (D), R1.1, R2.1, R3.1, R4.1, R7.1, R8.1, R10.1, R11.1, R14.2, U1.14 (VCC), U2.14 (VCC), U3.4 (~S), U3.10 (~S), U3.14 (VCC), U4.14 (VCC), U5.4 (~S), U5.10 (~S), U5.14 (VCC), U6.14 (VCC), U7.4 (R), U7.10 (R), U7.14 (VCC), U8.14 (VCC), U10.14 (VCC), X1.8 (Vcc); also elsewhere on the board
XO: SW2.1 (A), X1.5 (OUT)
~CLK_RST~: U1.10, U3.1 (~R), U3.13 (~R), U4.2, U5.1 (~R), U5.13 (~R)
~RST_HDR~: D3.1 (K), D5.1 (K), R1.2, SW4.2

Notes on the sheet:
Reset signals
TODO: put PHI_2 on the bus - bus devices could use this to ensure that they have a consistent view on what the effective clock speed of the system Maybe put it at A28 and move BASE_CLK to C31 to replace ~RST_HDR~ ~RST_HDR~ is unnecessary as the reset signal is handled by a header on the backplane
Soft power
Reverse voltage protection
TODO: overvoltage protection (not doing this for now)
BASE_CLK is the clock signal generated by the crystal oscillator or the 555 PHI_2 is the effective clock signal, which may be controlled by a bus device if ~BUS_ACTIVE~ is low
Clock switcher
shorter clock rst pulse s.t. clock starts before other ICs
